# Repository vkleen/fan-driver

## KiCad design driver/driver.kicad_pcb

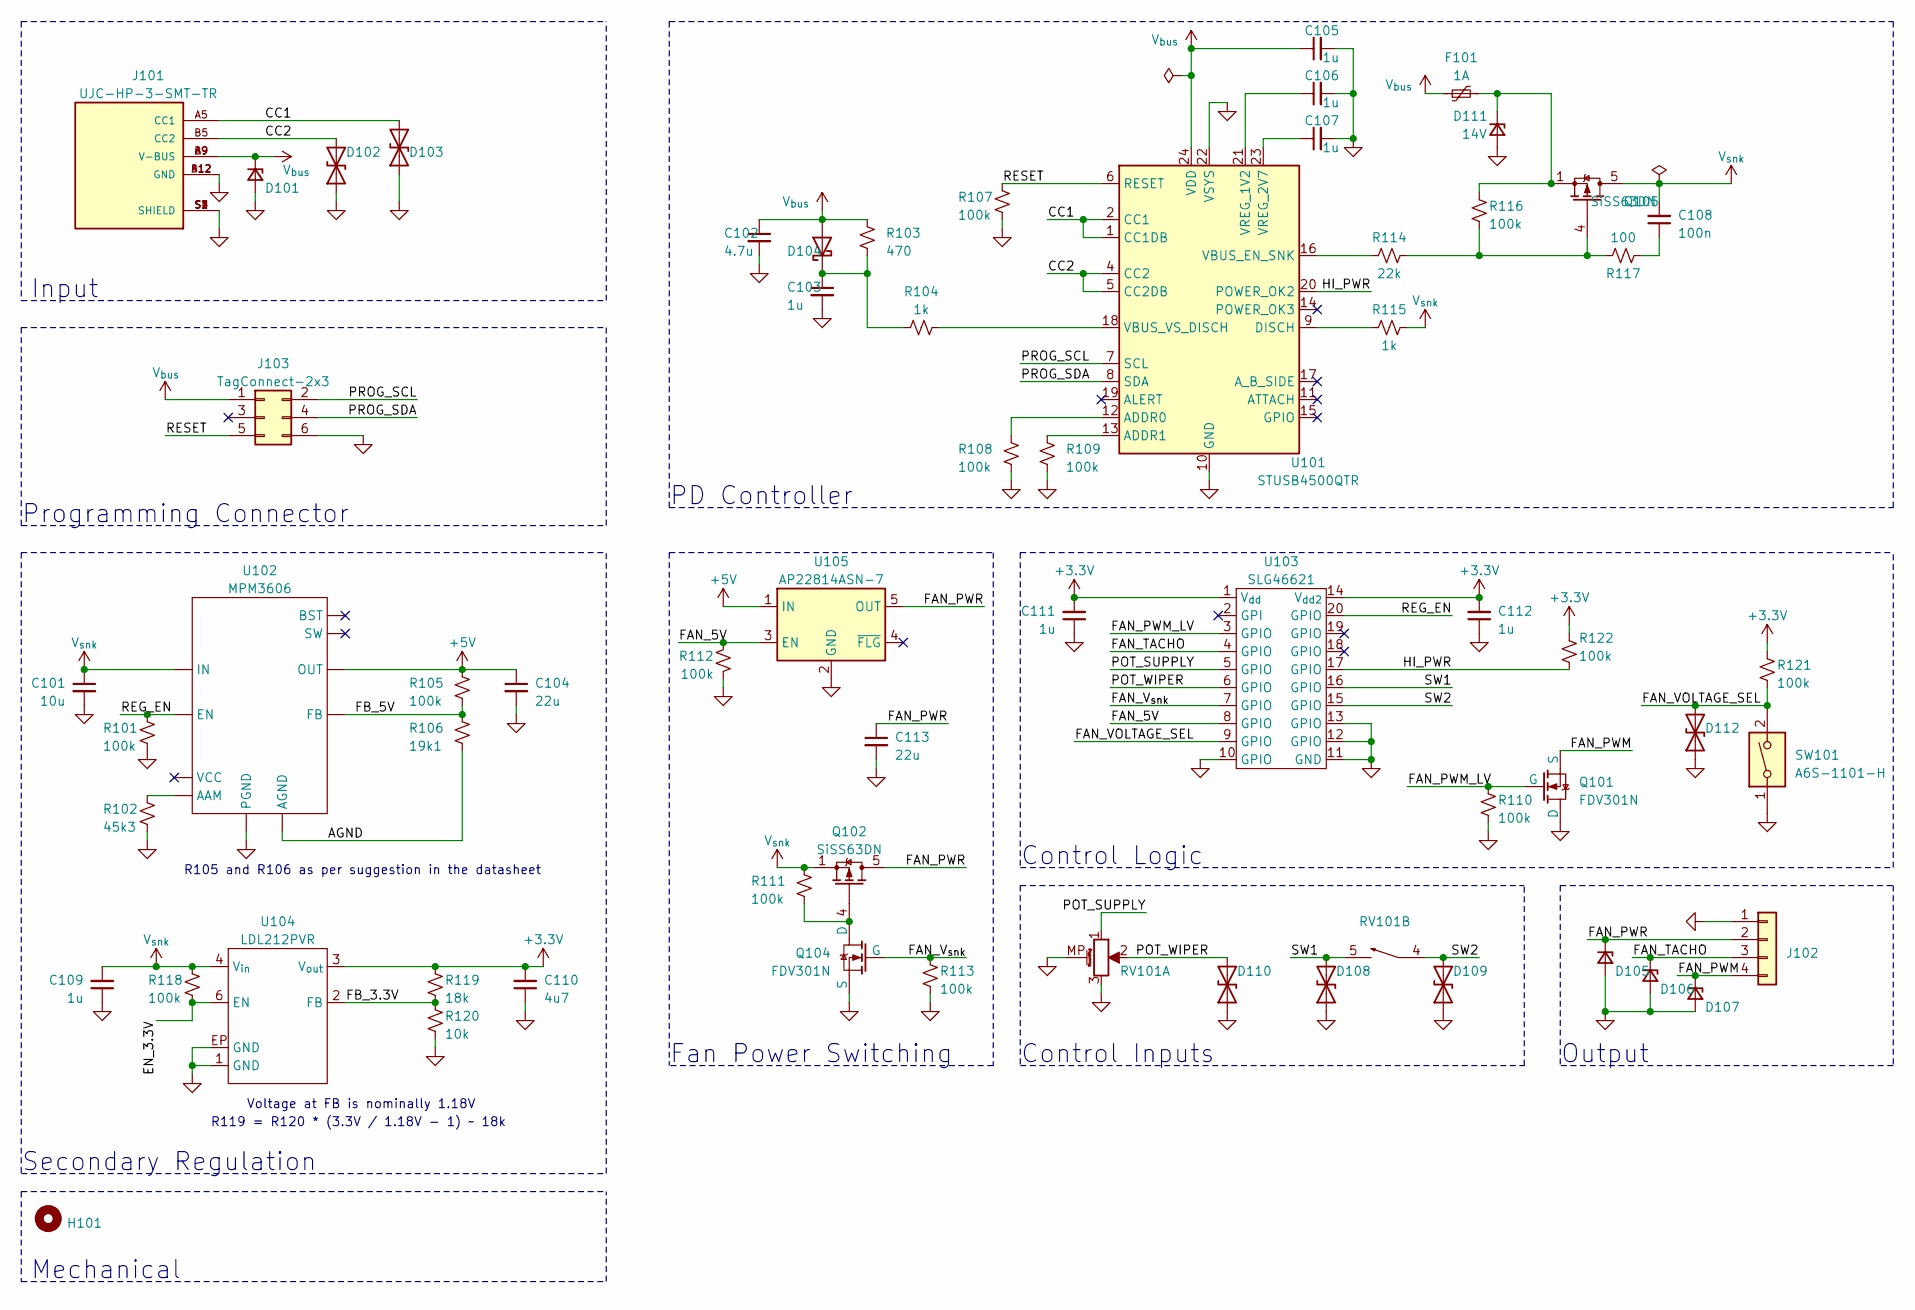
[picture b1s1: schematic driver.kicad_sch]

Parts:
C101: 10u; C_0805_2012Metric
C102: 4.7u; C_0805_2012Metric
C103, C105, C106, C107, C109, C111, C112: 1u; C_0402_1005Metric
C104, C113: 22u; C_0805_2012Metric
C108: 100n; C_0402_1005Metric
C110: 4u7; C_0805_2012Metric
D101, D105, D106, D107: uclamp2271p; uClampxx71P
D102, D103, D108, D109, D110, D112: uclamp2411za; uClamp2411ZA
D104: D_Schottky; Schottky_0402
D111: 14V; SOT-23
F101: 1A; R_0805_2012Metric
H101: MountingHole; MountingHole_5mm
J101: UJC-HP-3-SMT-TR
J102: fan_header_4pin; fan_header_4pin_right_angle
J103: TagConnect-2x3; Tag-Connect_TC2030-IDC-NL_2x03_P1.27mm_Vertical
Q101, Q104: FDV301N; SOT-23
Q102, Q105: SiSS63DN; Vishay_PowerPAK_1212-8_Single
R101, R105, R107, R108, R109, R110, R111, R112, R113, R116, R118, R121, R122: 100k; R_0402_1005Metric
R102: 45k3; R_0402_1005Metric
R103: 470; R_0402_1005Metric
R104, R115: 1k; R_0402_1005Metric
R106: 19k1; R_0402_1005Metric
R114: 22k; R_0402_1005Metric
R117: 100; R_0402_1005Metric
R119: 18k; R_0402_1005Metric
R120: 10k; R_0402_1005Metric
RV101: RK1191114001
SW101: A6S-1101-H
U101: STUSB4500QTR; QFN-24-1EP_4x4mm_P0.5mm_EP2.7x2.7mm
U102: MPM3606
U103: SLG46621; SLG46621V
U104: LDL212PVR
U105: AP22814ASN-7; Diodes_UDFN2020-6

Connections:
+3.3V: C110.2, C111.2, C112.2, R119.1, R121.1, R122.1, U103.1 (V_{dd}), U103.14 (V_{dd2}), U104.3 (V_{out})
+5V: C104.1, R105.1, U102.7,8,9 (OUT), U105.1 (IN)
/AGND: R106.2, U102.3 (AGND)
/CC1: D103.2 (A2), J101.A5 (CC1), U101.1 (CC1DB), U101.2 (CC1)
/CC2: D102.2 (A2), J101.B5 (CC2), U101.4 (CC2), U101.5 (CC2DB)
/EN_3.3V: R118.2, U104.6 (EN)
/FAN_5V: R112.1, U103.8 (GPIO), U105.3 (EN)
/FAN_PWM: D107.1 (K), J102.4, Q101.2 (S)
/FAN_PWM_LV: Q101.1 (G), R110.1, U103.3 (GPIO)
/FAN_PWR: C113.1, D105.1 (K), J102.2, Q102.5 (D), U105.5 (OUT)
/FAN_TACHO: D106.1 (K), J102.3, U103.4 (GPIO)
/FAN_VOLTAGE_SEL: D112.2 (A2), R121.2, SW101.2, U103.9 (GPIO)
/FAN_V_{snk}: Q104.1 (G), R113.1, U103.7 (GPIO)
/FB_3.3V: R119.2, R120.1, U104.2 (FB)
/FB_5V: R105.2, R106.1, U102.1 (FB)
/HI_PWR: R122.2, U101.20 (POWER_OK2), U103.17 (GPIO)
/POT_SUPPLY: RV101.1, U103.5 (GPIO)
/POT_WIPER: D110.2 (A2), RV101.2, U103.6 (GPIO)
/PROG_SCL: J103.2, U101.7 (SCL)
/PROG_SDA: J103.4, U101.8 (SDA)
/REG_EN: R101.1, U102.17 (EN), U103.20 (GPIO)
/RESET: J103.5, R107.1, U101.6 (RESET)
/SW1: D108.2 (A2), RV101.5, U103.16 (GPIO)
/SW2: D109.2 (A2), RV101.4, U103.15 (GPIO)
GND: C101.2, C102.2, C103.2, C104.2, C105.2, C106.2, C107.2, C109.1, C110.1, C111.1, C112.1, C113.2, D101.2 (A), D102.1 (A1), D103.1 (A1), D105.2 (A), D106.2 (A), D107.2 (A), D108.1 (A1), D109.1 (A1), D110.1 (A1), D111.1 (A), D112.1 (A1), J101.A12 (GND), J101.B12 (GND), J101.S1 (SHIELD), J101.S2 (SHIELD), J101.S3 (SHIELD), J101.S4 (SHIELD), J102.1, J103.6, Q101.3 (D), Q104.2 (S), R101.2, R102.2, R107.2, R108.2, R109.2, R110.2, R112.2, R113.2, R120.2, RV101.3, RV101.MP (MountPin), SW101.1, U101.10 (GND), U101.22 (VSYS), U101.25 (GND), U102.12 (PGND), U102.13 (PGND), U102.14 (PGND), U103.10 (GPIO), U103.11 (GND), U103.12 (GPIO), U103.13 (GPIO), U104.1 (GND), U104.EP (GND), U105.2 (GND), U105.EP (GND)
unnamed: C103.1, D104.1 (K), R103.2, R104.1
unnamed: C106.1, U101.21 (VREG_1V2)
unnamed: C107.1, U101.23 (VREG_2V7)
unnamed: C108.1, R117.2
unnamed: D111.3 (K), F101.2, Q105.1 (S), Q105.2 (S), Q105.3 (S), R116.1
unnamed: Q102.4 (G), Q104.3 (D), R111.2
unnamed: Q105.4 (G), R114.2, R116.2, R117.1
unnamed: R102.1, U102.18 (AAM)
unnamed: R104.2, U101.18 (VBUS_VS_DISCH)
unnamed: R108.1, U101.12 (ADDR0)
unnamed: R109.1, U101.13 (ADDR1)
unnamed: R114.1, U101.16 (VBUS_EN_SNK)
unnamed: R115.1, U101.9 (DISCH)
V_{bus}: C102.1, C105.1, D101.1 (K), D104.2 (A), F101.1, J101.A9 (V-BUS), J101.B9 (V-BUS), J103.1, R103.1, U101.24 (VDD)
V_{snk}: C101.1, C108.2, C109.2, Q102.1 (S), Q102.2 (S), Q102.3 (S), Q105.5 (D), R111.1, R115.2, R118.1, U102.16 (IN), U104.4 (V_{in})

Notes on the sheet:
Programming Connector
Secondary Regulation
Input
Mechanical
R105 and R106 as per suggestion in the datasheet
R119 = R120 * (3.3V / 1.18V - 1) ~~ 18k
Voltage at FB is nominally 1.18V
PD Controller
Fan Power Switching
Control Logic
Control Inputs
Output

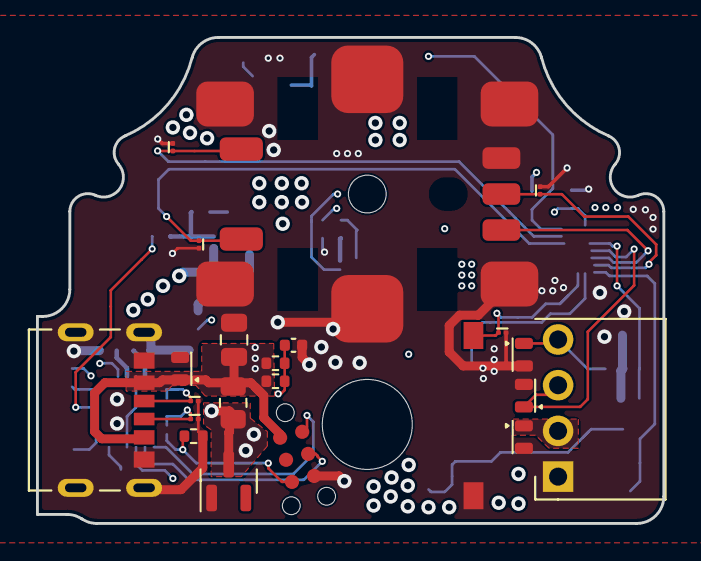
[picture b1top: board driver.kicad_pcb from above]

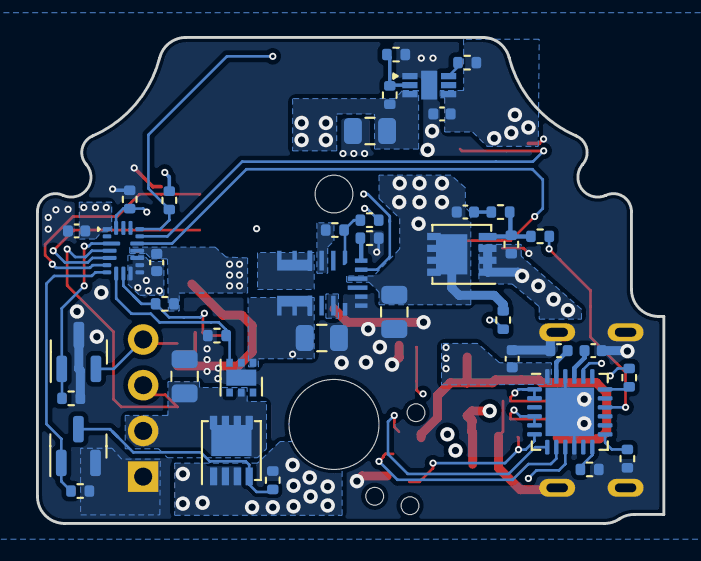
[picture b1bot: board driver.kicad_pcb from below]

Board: 4 copper layers, 34.8 x 27.0 mm, 63 parts (40 on the bottom side), 40 nets.

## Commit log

2021-06-16 start design
2021-06-17 Start placing connectors
2021-06-18 First PCB routing
2021-06-18 Add PDF schematic
2021-06-18 Change the 5V power switch mosfet to a controller with reverse voltage protection
2021-06-18 Fix board setup
2021-06-18 Add interactive bom
2021-06-18 FAN_PWM: guard against high voltage from the fan
